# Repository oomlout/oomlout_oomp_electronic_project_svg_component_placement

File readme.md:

# SVG Component Placement in Kicad
Placing components along a path in Kicad.
##notes
Placing components along a path in Kicad.  
* ibom github: [ibom github](kicad\current_version\working\bom\ibom.html)
* ibom direct: [ibom direct](https://raw.githack.com/oomlout/oomlout_oomp_electronic_project_svg_component_placement/main/kicad/current_version/working/bom/ibom.html)

## pcb  

[board (pdf)](kicad/current_version/working/working.pdf)  

## corel working

## oomp_parts_summary
| index | designator | quantity | oomp_id | 
| --- | --- | --- | --- | 
| 1 | L2,L12,L35,L165,L51,L37,L11,L80,L14,L94,L134,L69,L193,L36,L23,L22,L180,L82,L30,L107,L181,L20,L15,L102,L55,L71,L43,L148,L145,L158,L53,L98,L166,L155,L49,L18,L146,L111,L33,L40,L81,L183,L75,L171,L143,L24,L167,L64,L38,L41,L59,L117,L105,L120,L142,L164,L84,L156,L108,L176,L130,L168,L151,L45,L114,L54,L29,L133,L42,L79,L74,L135,L144,L31,L87,L17,L66,L106,L159,L70,L149,L138,L161,L44,L123,L100,L188,L83,L6,L89,L34,L137,L67,L73,L103,L95,L60,L154,L13,L184,L16,L152,L9,L1,L190,L192,L77,L86,L173,L124,L101,L136,L194,L147,L26,L62,L179,L56,L160,L128,L196,L141,L178,L104,L115,L177,L109,L185,L191,L157,L169,L112,L10,L126,L131,L72,L19,L58,L99,L5,L91,L195,L125,L85,L27,L189,L187,L7,L57,L121,L163,L32,L93,L197,L88,L3,L186,L153,L25,L61,L21,L68,L110,L162,L119,L48,L139,L170,L47,L76,L97,L175,L50,L4,L96,L140,L113,L172,L39,L65,L90,L150,L118,L174,L78,L129,L28,L132,L52,L63,L122,L182,L92,L46,L127,L8,L116 | 197 | electronic_led_0603_red | 
| 2 | CON1 | 1 | electronic_header_2_54_mm_2_pin_through_hole | 

Search Links: (L) - lcsc, (D) - digikey, (M) - mouser, (N) - newark, (SZ) - szlcsc
note: a work on progress that takes the bom file from kicad pcb and try's to add oomp details

## positions
### top
| # Ref | Val | Package | PosX | PosY | Rot | Side | 
| --- | --- | --- | --- | --- | --- | --- | 
| CON1 | hi12pth | hi12pth_electronic_header_2_54_mm_2_pin_through_hole | -30.5 | -239.5 | 0.0 | top | 
| L1 | l6r | l6r_electronic_led_0603_red | 18.6027 | -161.0 | -135.0002 | top | 
| L2 | l6r | l6r_electronic_led_0603_red | 14.7455 | -161.0 | -135.0002 | top | 
| L3 | l6r | l6r_electronic_led_0603_red | 10.8882 | -161.0 | -135.0002 | top | 
| L4 | l6r | l6r_electronic_led_0603_red | 7.031 | -161.0 | -135.0002 | top | 
| L5 | l6r | l6r_electronic_led_0603_red | 3.1737 | -161.0 | -135.0002 | top | 
| L6 | l6r | l6r_electronic_led_0603_red | -0.6836 | -161.0 | -135.0002 | top | 
| L7 | l6r | l6r_electronic_led_0603_red | -4.5408 | -161.0 | -135.0002 | top | 
| L8 | l6r | l6r_electronic_led_0603_red | -8.3981 | -161.0 | -135.0002 | top | 
| L9 | l6r | l6r_electronic_led_0603_red | -12.2553 | -161.0 | -135.0002 | top | 
| L10 | l6r | l6r_electronic_led_0603_red | -16.1126 | -161.0 | -135.0002 | top | 
| L11 | l6r | l6r_electronic_led_0603_red | -19.9698 | -161.0 | -135.0002 | top | 
| L12 | l6r | l6r_electronic_led_0603_red | -22.45 | -162.3771 | -45.0001 | top | 
| L13 | l6r | l6r_electronic_led_0603_red | -20.8956 | -164.68 | 45.0 | top | 
| L14 | l6r | l6r_electronic_led_0603_red | -17.0384 | -164.68 | 45.0 | top | 
| L15 | l6r | l6r_electronic_led_0603_red | -13.1811 | -164.68 | 45.0 | top | 
| L16 | l6r | l6r_electronic_led_0603_red | -9.3239 | -164.68 | 45.0 | top | 
| L17 | l6r | l6r_electronic_led_0603_red | -5.4666 | -164.68 | 45.0 | top | 
| L18 | l6r | l6r_electronic_led_0603_red | -1.6093 | -164.68 | 45.0 | top | 
| L19 | l6r | l6r_electronic_led_0603_red | 2.2479 | -164.68 | 45.0 | top | 
| L20 | l6r | l6r_electronic_led_0603_red | 6.1052 | -164.68 | 45.0 | top | 
| L21 | l6r | l6r_electronic_led_0603_red | 9.9624 | -164.68 | 45.0 | top | 
| L22 | l6r | l6r_electronic_led_0603_red | 13.8324 | -164.696 | 36.9786 | top | 
| L23 | l6r | l6r_electronic_led_0603_red | 16.4655 | -167.1062 | -34.3104 | top | 
| L24 | l6r | l6r_electronic_led_0603_red | 15.5131 | -170.8008 | -66.5478 | top | 
| L25 | l6r | l6r_electronic_led_0603_red | 14.0972 | -174.3888 | -66.5202 | top | 
| L26 | l6r | l6r_electronic_led_0603_red | 12.6822 | -177.9772 | -66.5202 | top | 
| L27 | l6r | l6r_electronic_led_0603_red | 11.2673 | -181.5655 | -66.5202 | top | 
| L28 | l6r | l6r_electronic_led_0603_red | 9.8523 | -185.1539 | -66.5202 | top | 
| L29 | l6r | l6r_electronic_led_0603_red | 8.4374 | -188.7423 | -66.5202 | top | 
| L30 | l6r | l6r_electronic_led_0603_red | 7.0224 | -192.3306 | -66.5202 | top | 
| L31 | l6r | l6r_electronic_led_0603_red | 5.6075 | -195.919 | -66.5202 | top | 
| L32 | l6r | l6r_electronic_led_0603_red | 4.1925 | -199.5074 | -66.5202 | top | 
| L33 | l6r | l6r_electronic_led_0603_red | 2.7776 | -203.0957 | -66.5202 | top | 
| L34 | l6r | l6r_electronic_led_0603_red | 1.3626 | -206.6841 | -66.5202 | top | 
| L35 | l6r | l6r_electronic_led_0603_red | -0.0523 | -210.2725 | -66.5202 | top | 
| L36 | l6r | l6r_electronic_led_0603_red | -1.4673 | -213.8608 | -66.5202 | top | 
| L37 | l6r | l6r_electronic_led_0603_red | -2.8822 | -217.4492 | -66.5202 | top | 
| L38 | l6r | l6r_electronic_led_0603_red | -4.2971 | -221.0376 | -66.5202 | top | 
| L39 | l6r | l6r_electronic_led_0603_red | -5.7121 | -224.6259 | -66.5202 | top | 
| L40 | l6r | l6r_electronic_led_0603_red | -7.127 | -228.2143 | -66.5202 | top | 
| L41 | l6r | l6r_electronic_led_0603_red | -8.542 | -231.8027 | -66.5202 | top | 
| L42 | l6r | l6r_electronic_led_0603_red | -9.9569 | -235.391 | -66.5202 | top | 
| L43 | l6r | l6r_electronic_led_0603_red | -11.3719 | -238.9794 | -12.6917 | top | 
| L44 | l6r | l6r_electronic_led_0603_red | -7.5449 | -239.0 | 45.0 | top | 
| L45 | l6r | l6r_electronic_led_0603_red | -5.2221 | -236.7462 | 113.4976 | top | 
| L46 | l6r | l6r_electronic_led_0603_red | -3.8083 | -233.1574 | 113.4976 | top | 
| L47 | l6r | l6r_electronic_led_0603_red | -2.3944 | -229.5686 | 113.4976 | top | 
| L48 | l6r | l6r_electronic_led_0603_red | -0.9806 | -225.9798 | 113.4976 | top | 
| L49 | l6r | l6r_electronic_led_0603_red | 0.4333 | -222.391 | 113.4976 | top | 
| L50 | l6r | l6r_electronic_led_0603_red | 1.8471 | -218.8022 | 113.4976 | top | 
| L51 | l6r | l6r_electronic_led_0603_red | 3.261 | -215.2134 | 113.4976 | top | 
| L52 | l6r | l6r_electronic_led_0603_red | 4.6748 | -211.6246 | 113.4976 | top | 
| L53 | l6r | l6r_electronic_led_0603_red | 6.0887 | -208.0358 | 113.4976 | top | 
| L54 | l6r | l6r_electronic_led_0603_red | 7.5025 | -204.447 | 113.4976 | top | 
| L55 | l6r | l6r_electronic_led_0603_red | 8.9164 | -200.8582 | 113.4976 | top | 
| L56 | l6r | l6r_electronic_led_0603_red | 10.3302 | -197.2694 | 113.4976 | top | 
| L57 | l6r | l6r_electronic_led_0603_red | 11.744 | -193.6806 | 113.4976 | top | 
| L58 | l6r | l6r_electronic_led_0603_red | 13.1579 | -190.0918 | 113.4976 | top | 
| L59 | l6r | l6r_electronic_led_0603_red | 14.5717 | -186.503 | 113.4976 | top | 
| L60 | l6r | l6r_electronic_led_0603_red | 15.9856 | -182.9142 | 113.4976 | top | 
| L61 | l6r | l6r_electronic_led_0603_red | 17.3994 | -179.3254 | 113.4976 | top | 
| L62 | l6r | l6r_electronic_led_0603_red | 18.8133 | -175.7366 | 113.4976 | top | 
| L63 | l6r | l6r_electronic_led_0603_red | 20.2271 | -172.1478 | 113.4976 | top | 
| L64 | l6r | l6r_electronic_led_0603_red | 21.641 | -168.559 | 113.4976 | top | 
| L65 | l6r | l6r_electronic_led_0603_red | 22.46 | -164.8573 | 135.0001 | top | 
| L66 | l6r | l6r_electronic_led_0603_red | -28.46 | -155.0 | 45.0 | top | 
| L67 | l6r | l6r_electronic_led_0603_red | -23.854 | -155.0 | 45.0 | top | 
| L68 | l6r | l6r_electronic_led_0603_red | -19.2479 | -155.0 | 45.0 | top | 
| L69 | l6r | l6r_electronic_led_0603_red | -14.6419 | -155.0 | 45.0 | top | 
| L70 | l6r | l6r_electronic_led_0603_red | -10.0358 | -155.0 | 45.0 | top | 
| L71 | l6r | l6r_electronic_led_0603_red | -5.4298 | -155.0 | 45.0 | top | 
| L72 | l6r | l6r_electronic_led_0603_red | -0.8237 | -155.0 | 45.0 | top | 
| L73 | l6r | l6r_electronic_led_0603_red | 3.7823 | -155.0 | 45.0 | top | 
| L74 | l6r | l6r_electronic_led_0603_red | 8.3884 | -155.0 | 45.0 | top | 
| L75 | l6r | l6r_electronic_led_0603_red | 12.9944 | -155.0 | 45.0 | top | 
| L76 | l6r | l6r_electronic_led_0603_red | 17.6005 | -155.0 | 45.0 | top | 
| L77 | l6r | l6r_electronic_led_0603_red | 22.2065 | -155.0 | 45.0 | top | 
| L78 | l6r | l6r_electronic_led_0603_red | 26.8126 | -155.0 | 45.0 | top | 
| L79 | l6r | l6r_electronic_led_0603_red | 28.46 | -157.9586 | -45.0001 | top | 
| L80 | l6r | l6r_electronic_led_0603_red | 28.46 | -162.5646 | -45.0001 | top | 
| L81 | l6r | l6r_electronic_led_0603_red | 28.46 | -167.1707 | -51.7968 | top | 
| L82 | l6r | l6r_electronic_led_0603_red | 26.9252 | -171.4853 | -66.5048 | top | 
| L83 | l6r | l6r_electronic_led_0603_red | 25.2368 | -175.7707 | -66.5048 | top | 
| L84 | l6r | l6r_electronic_led_0603_red | 23.5483 | -180.0561 | -66.5048 | top | 
| L85 | l6r | l6r_electronic_led_0603_red | 21.8598 | -184.3415 | -66.5048 | top | 
| L86 | l6r | l6r_electronic_led_0603_red | 20.1713 | -188.6269 | -66.5048 | top | 
| L87 | l6r | l6r_electronic_led_0603_red | 18.4829 | -192.9123 | -66.5048 | top | 
| L88 | l6r | l6r_electronic_led_0603_red | 16.7944 | -197.1977 | -66.5048 | top | 
| L89 | l6r | l6r_electronic_led_0603_red | 15.1059 | -201.4831 | -66.5048 | top | 
| L90 | l6r | l6r_electronic_led_0603_red | 13.4174 | -205.7685 | -66.5048 | top | 
| L91 | l6r | l6r_electronic_led_0603_red | 11.729 | -210.0539 | -66.5048 | top | 
| L92 | l6r | l6r_electronic_led_0603_red | 10.0405 | -214.3394 | -66.5048 | top | 
| L93 | l6r | l6r_electronic_led_0603_red | 8.352 | -218.6248 | -66.5048 | top | 
| L94 | l6r | l6r_electronic_led_0603_red | 6.6635 | -222.9102 | -66.5048 | top | 
| L95 | l6r | l6r_electronic_led_0603_red | 4.9751 | -227.1956 | -66.5048 | top | 
| L96 | l6r | l6r_electronic_led_0603_red | 3.2866 | -231.481 | -66.5048 | top | 
| L97 | l6r | l6r_electronic_led_0603_red | 1.5981 | -235.7664 | -66.5048 | top | 
| L98 | l6r | l6r_electronic_led_0603_red | -0.0904 | -240.0518 | -66.5048 | top | 
| L99 | l6r | l6r_electronic_led_0603_red | -1.7789 | -244.3372 | -77.912 | top | 
| L100 | l6r | l6r_electronic_led_0603_red | -5.9337 | -245.0 | -135.0002 | top | 
| L101 | l6r | l6r_electronic_led_0603_red | -10.5397 | -245.0 | -135.0002 | top | 
| L102 | l6r | l6r_electronic_led_0603_red | -15.1457 | -245.0 | -135.0002 | top | 
| L103 | l6r | l6r_electronic_led_0603_red | -19.7518 | -245.0 | -161.549 | top | 
| L104 | l6r | l6r_electronic_led_0603_red | -18.6614 | -241.1226 | 113.4837 | top | 
| L105 | l6r | l6r_electronic_led_0603_red | -16.972 | -236.8375 | 113.4837 | top | 
| L106 | l6r | l6r_electronic_led_0603_red | -15.2827 | -232.5525 | 113.4837 | top | 
| L107 | l6r | l6r_electronic_led_0603_red | -13.5933 | -228.2674 | 113.4837 | top | 
| L108 | l6r | l6r_electronic_led_0603_red | -11.904 | -223.9824 | 113.4837 | top | 
| L109 | l6r | l6r_electronic_led_0603_red | -10.2146 | -219.6973 | 113.4837 | top | 
| L110 | l6r | l6r_electronic_led_0603_red | -8.5253 | -215.4122 | 113.4837 | top | 
| L111 | l6r | l6r_electronic_led_0603_red | -6.8359 | -211.1272 | 113.4837 | top | 
| L112 | l6r | l6r_electronic_led_0603_red | -5.1466 | -206.8421 | 113.4837 | top | 
| L113 | l6r | l6r_electronic_led_0603_red | -3.4572 | -202.557 | 113.4837 | top | 
| L114 | l6r | l6r_electronic_led_0603_red | -1.7679 | -198.272 | 113.4837 | top | 
| L115 | l6r | l6r_electronic_led_0603_red | -0.0785 | -193.9869 | 113.4837 | top | 
| L116 | l6r | l6r_electronic_led_0603_red | 1.6108 | -189.7019 | 113.4837 | top | 
| L117 | l6r | l6r_electronic_led_0603_red | 3.3001 | -185.4168 | 113.4837 | top | 
| L118 | l6r | l6r_electronic_led_0603_red | 4.9895 | -181.1317 | 113.4837 | top | 
| L119 | l6r | l6r_electronic_led_0603_red | 6.6788 | -176.8467 | 113.4837 | top | 
| L120 | l6r | l6r_electronic_led_0603_red | 8.3682 | -172.5616 | 113.4837 | top | 
| L121 | l6r | l6r_electronic_led_0603_red | 6.5265 | -170.68 | -135.0002 | top | 
| L122 | l6r | l6r_electronic_led_0603_red | 1.9205 | -170.68 | -135.0002 | top | 
| L123 | l6r | l6r_electronic_led_0603_red | -2.6856 | -170.68 | -135.0002 | top | 
| L124 | l6r | l6r_electronic_led_0603_red | -7.2916 | -170.68 | -135.0002 | top | 
| L125 | l6r | l6r_electronic_led_0603_red | -11.8977 | -170.68 | -135.0002 | top | 
| L126 | l6r | l6r_electronic_led_0603_red | -16.5037 | -170.68 | -135.0002 | top | 
| L127 | l6r | l6r_electronic_led_0603_red | -21.1098 | -170.68 | -135.0002 | top | 
| L128 | l6r | l6r_electronic_led_0603_red | -25.7158 | -170.68 | -135.0002 | top | 
| L129 | l6r | l6r_electronic_led_0603_red | -28.46 | -168.8181 | 135.0001 | top | 
| L130 | l6r | l6r_electronic_led_0603_red | -28.46 | -164.2121 | 135.0001 | top | 
| L131 | l6r | l6r_electronic_led_0603_red | -28.46 | -159.606 | 135.0001 | top | 
| L132 | l6r | l6r_electronic_led_0603_red | 25.46 | -158.0 | -135.0002 | top | 
| L133 | l6r | l6r_electronic_led_0603_red | 21.2057 | -158.0 | -135.0002 | top | 
| L134 | l6r | l6r_electronic_led_0603_red | 16.9514 | -158.0 | -135.0002 | top | 
| L135 | l6r | l6r_electronic_led_0603_red | 12.6971 | -158.0 | -135.0002 | top | 
| L136 | l6r | l6r_electronic_led_0603_red | 8.4428 | -158.0 | -135.0002 | top | 
| L137 | l6r | l6r_electronic_led_0603_red | 4.1885 | -158.0 | -135.0002 | top | 
| L138 | l6r | l6r_electronic_led_0603_red | -0.0658 | -158.0 | -135.0002 | top | 
| L139 | l6r | l6r_electronic_led_0603_red | -4.3201 | -158.0 | -135.0002 | top | 
| L140 | l6r | l6r_electronic_led_0603_red | -8.5744 | -158.0 | -135.0002 | top | 
| L141 | l6r | l6r_electronic_led_0603_red | -12.8287 | -158.0 | -135.0002 | top | 
| L142 | l6r | l6r_electronic_led_0603_red | -17.083 | -158.0 | -135.0002 | top | 
| L143 | l6r | l6r_electronic_led_0603_red | -21.3373 | -158.0 | -135.0002 | top | 
| L144 | l6r | l6r_electronic_led_0603_red | -25.46 | -158.1316 | -82.9445 | top | 
| L145 | l6r | l6r_electronic_led_0603_red | -25.46 | -162.3859 | -45.0001 | top | 
| L146 | l6r | l6r_electronic_led_0603_red | -25.46 | -166.6402 | -44.3512 | top | 
| L147 | l6r | l6r_electronic_led_0603_red | -22.2455 | -167.68 | 45.0 | top | 
| L148 | l6r | l6r_electronic_led_0603_red | -17.9911 | -167.68 | 45.0 | top | 
| L149 | l6r | l6r_electronic_led_0603_red | -13.7368 | -167.68 | 45.0 | top | 
| L150 | l6r | l6r_electronic_led_0603_red | -9.4825 | -167.68 | 45.0 | top | 
| L151 | l6r | l6r_electronic_led_0603_red | -5.2282 | -167.68 | 45.0 | top | 
| L152 | l6r | l6r_electronic_led_0603_red | -0.9739 | -167.68 | 45.0 | top | 
| L153 | l6r | l6r_electronic_led_0603_red | 3.2804 | -167.68 | 45.0 | top | 
| L154 | l6r | l6r_electronic_led_0603_red | 7.5347 | -167.68 | 45.0 | top | 
| L155 | l6r | l6r_electronic_led_0603_red | 11.789 | -167.68 | 45.0 | top | 
| L156 | l6r | l6r_electronic_led_0603_red | 12.5908 | -170.026 | -66.608 | top | 
| L157 | l6r | l6r_electronic_led_0603_red | 11.0279 | -173.9828 | -66.5112 | top | 
| L158 | l6r | l6r_electronic_led_0603_red | 9.4679 | -177.9407 | -66.5112 | top | 
| L159 | l6r | l6r_electronic_led_0603_red | 7.9079 | -181.8987 | -66.5112 | top | 
| L160 | l6r | l6r_electronic_led_0603_red | 6.348 | -185.8567 | -66.5112 | top | 
| L161 | l6r | l6r_electronic_led_0603_red | 4.788 | -189.8147 | -66.5112 | top | 
| L162 | l6r | l6r_electronic_led_0603_red | 3.228 | -193.7727 | -66.5112 | top | 
| L163 | l6r | l6r_electronic_led_0603_red | 1.668 | -197.7306 | -66.5112 | top | 
| L164 | l6r | l6r_electronic_led_0603_red | 0.1081 | -201.6886 | -66.5112 | top | 
| L165 | l6r | l6r_electronic_led_0603_red | -1.4519 | -205.6466 | -66.5112 | top | 
| L166 | l6r | l6r_electronic_led_0603_red | -3.0119 | -209.6046 | -66.5112 | top | 
| L167 | l6r | l6r_electronic_led_0603_red | -4.5718 | -213.5625 | -66.5112 | top | 
| L168 | l6r | l6r_electronic_led_0603_red | -6.1318 | -217.5205 | -66.5112 | top | 
| L169 | l6r | l6r_electronic_led_0603_red | -7.6918 | -221.4785 | -66.5112 | top | 
| L170 | l6r | l6r_electronic_led_0603_red | -9.2518 | -225.4365 | -66.5112 | top | 
| L171 | l6r | l6r_electronic_led_0603_red | -10.8117 | -229.3944 | -66.5112 | top | 
| L172 | l6r | l6r_electronic_led_0603_red | -12.3717 | -233.3524 | -66.5112 | top | 
| L173 | l6r | l6r_electronic_led_0603_red | -13.9317 | -237.3104 | -66.5112 | top | 
| L174 | l6r | l6r_electronic_led_0603_red | -15.4916 | -241.2684 | -58.1207 | top | 
| L175 | l6r | l6r_electronic_led_0603_red | -12.3121 | -242.0 | 45.0 | top | 
| L176 | l6r | l6r_electronic_led_0603_red | -8.0578 | -242.0 | 45.0 | top | 
| L177 | l6r | l6r_electronic_led_0603_red | -3.9723 | -241.752 | 88.9313 | top | 
| L178 | l6r | l6r_electronic_led_0603_red | -2.413 | -237.7938 | 113.4984 | top | 
| L179 | l6r | l6r_electronic_led_0603_red | -0.8537 | -233.8356 | 113.4984 | top | 
| L180 | l6r | l6r_electronic_led_0603_red | 0.7056 | -229.8773 | 113.4984 | top | 
| L181 | l6r | l6r_electronic_led_0603_red | 2.265 | -225.9191 | 113.4984 | top | 
| L182 | l6r | l6r_electronic_led_0603_red | 3.8243 | -221.9609 | 113.4984 | top | 
| L183 | l6r | l6r_electronic_led_0603_red | 5.3836 | -218.0026 | 113.4984 | top | 
| L184 | l6r | l6r_electronic_led_0603_red | 6.9429 | -214.0444 | 113.4984 | top | 
| L185 | l6r | l6r_electronic_led_0603_red | 8.5022 | -210.0862 | 113.4984 | top | 
| L186 | l6r | l6r_electronic_led_0603_red | 10.0616 | -206.1279 | 113.4984 | top | 
| L187 | l6r | l6r_electronic_led_0603_red | 11.6209 | -202.1697 | 113.4984 | top | 
| L188 | l6r | l6r_electronic_led_0603_red | 13.1802 | -198.2115 | 113.4984 | top | 
| L189 | l6r | l6r_electronic_led_0603_red | 14.7395 | -194.2532 | 113.4984 | top | 
| L190 | l6r | l6r_electronic_led_0603_red | 16.2988 | -190.295 | 113.4984 | top | 
| L191 | l6r | l6r_electronic_led_0603_red | 17.8582 | -186.3368 | 113.4984 | top | 
| L192 | l6r | l6r_electronic_led_0603_red | 19.4175 | -182.3785 | 113.4984 | top | 
| L193 | l6r | l6r_electronic_led_0603_red | 20.9768 | -178.4203 | 113.4984 | top | 
| L194 | l6r | l6r_electronic_led_0603_red | 22.5361 | -174.4621 | 113.4984 | top | 
| L195 | l6r | l6r_electronic_led_0603_red | 24.0954 | -170.5038 | 113.4984 | top | 
| L196 | l6r | l6r_electronic_led_0603_red | 25.46 | -166.5086 | 129.6684 | top | 
| L197 | l6r | l6r_electronic_led_0603_red | 25.46 | -162.2543 | 135.0001 | top | 

### bottom
no data

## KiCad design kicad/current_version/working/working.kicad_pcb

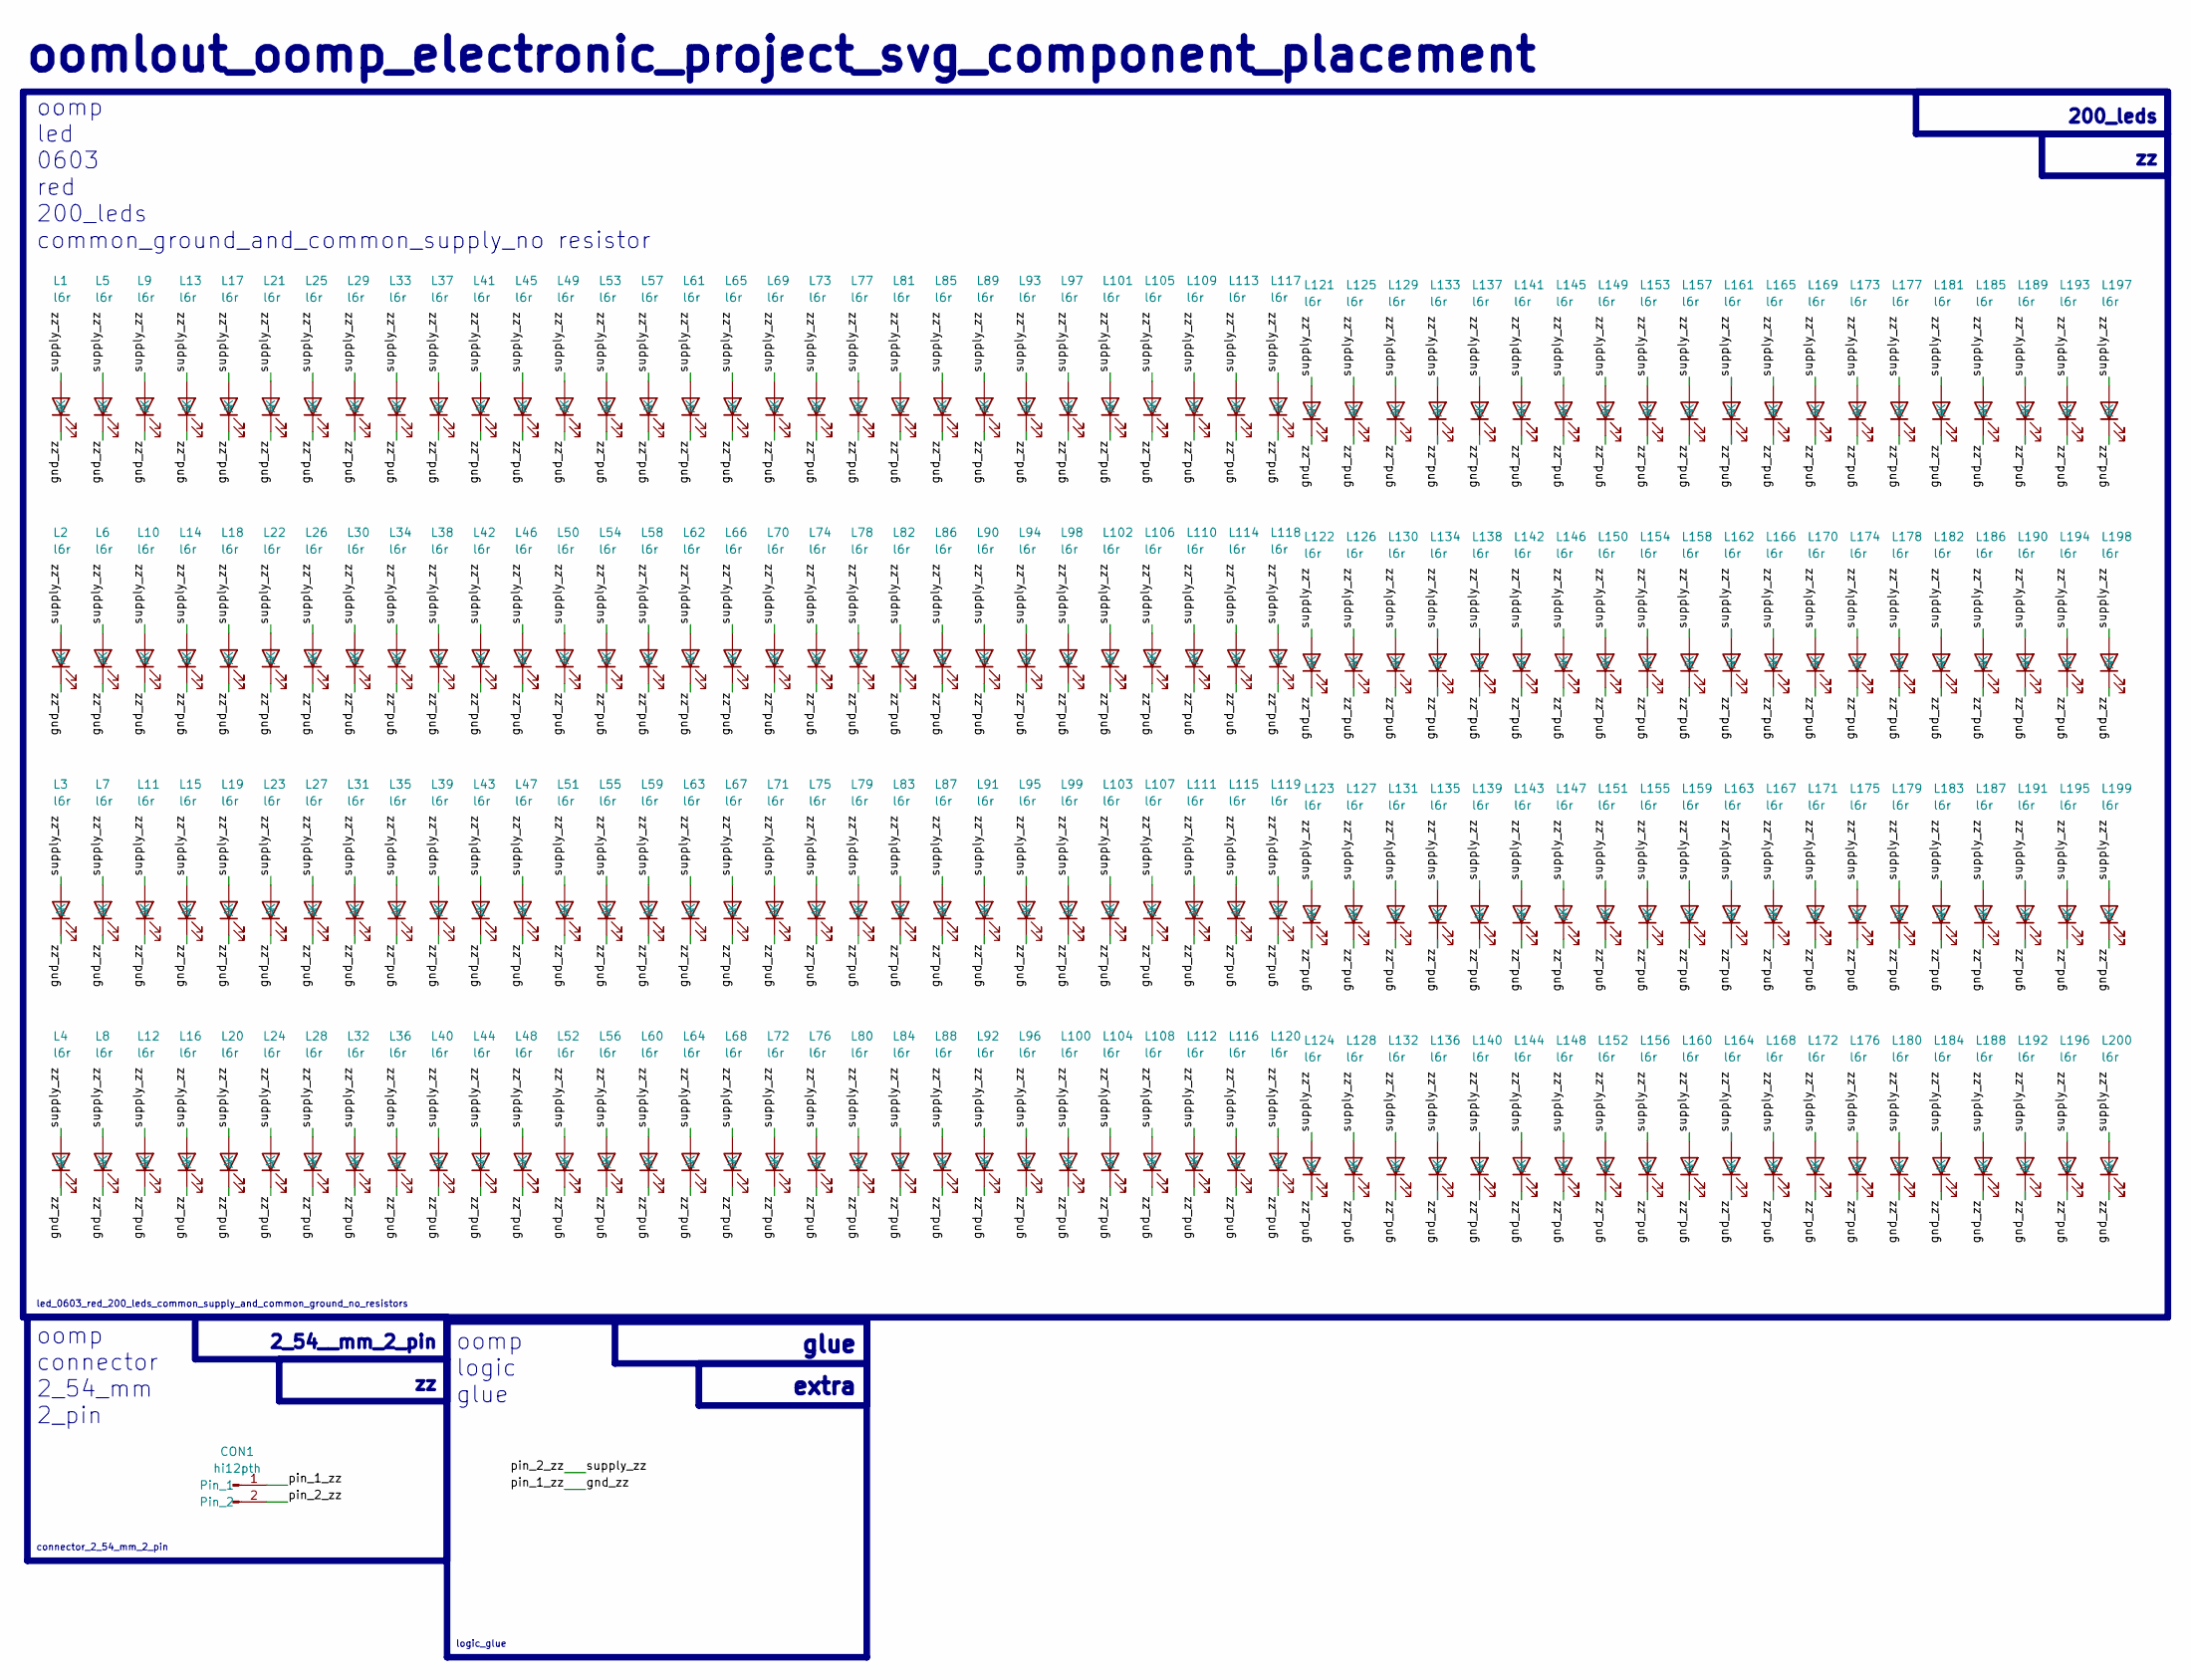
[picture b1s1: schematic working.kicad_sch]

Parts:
CON1: hi12pth; hi12pth_electronic_header_2_54_mm_2_pin_through_hole
L1, L2, L3, L4, L5, L6, L7, L8, L9, L10, L11, L12, L13, L14, L15, L16, L17, L18, L19, L20, L21, L22, L23, L24, L25, L26, L27, L28, L29, L30, L31, L32, L33, L34, L35, L36, L37, L38, L39, L40, L41, L42, L43, L44, L45, L46, L47, L48, L49, L50, L51, L52, L53, L54, L55, L56, L57, L58, L59, L60, L61, L62, L63, L64, L65, L66, L67, L68, L69, L70, L71, L72, L73, L74, L75, L76, L77, L78, L79, L80, L81, L82, L83, L84, L85, L86, L87, L88, L89, L90, L91, L92, L93, L94, L95, L96, L97, L98, L99, L100, L101, L102, L103, L104, L105, L106, L107, L108, L109, L110, L111, L112, L113, L114, L115, L116, L117, L118, L119, L120, L121, L122, L123, L124, L125, L126, L127, L128, L129, L130, L131, L132, L133, L134, L135, L136, L137, L138, L139, L140, L141, L142, L143, L144, L145, L146, L147, L148, L149, L150, L151, L152, L153, L154, L155, L156, L157, L158, L159, L160, L161, L162, L163, L164, L165, L166, L167, L168, L169, L170, L171, L172, L173, L174, L175, L176, L177, L178, L179, L180, L181, L182, L183, L184, L185, L186, L187, L188, L189, L190, L191, L192, L193, L194, L195, L196, L197, L198, L199, L200: l6r; l6r_electronic_led_0603_red

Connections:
/gnd_zz: CON1.1, L1.1 (K), L2.1 (K), L3.1 (K), L4.1 (K), L5.1 (K), L6.1 (K), L7.1 (K), L8.1 (K), L9.1 (K), L10.1 (K), L11.1 (K), L12.1 (K), L13.1 (K), L14.1 (K), L15.1 (K), L16.1 (K), L17.1 (K), L18.1 (K), L19.1 (K), L20.1 (K), L21.1 (K), L22.1 (K), L23.1 (K), L24.1 (K), L25.1 (K), L26.1 (K), L27.1 (K), L28.1 (K), L29.1 (K), L30.1 (K), L31.1 (K), L32.1 (K), L33.1 (K), L34.1 (K), L35.1 (K), L36.1 (K), L37.1 (K), L38.1 (K), L39.1 (K), L40.1 (K), L41.1 (K), L42.1 (K), L43.1 (K), L44.1 (K), L45.1 (K), L46.1 (K), L47.1 (K), L48.1 (K), L49.1 (K), L50.1 (K), L51.1 (K), L52.1 (K), L53.1 (K), L54.1 (K), L55.1 (K), L56.1 (K), L57.1 (K), L58.1 (K), L59.1 (K), L60.1 (K), L61.1 (K), L62.1 (K), L63.1 (K), L64.1 (K), L65.1 (K), L66.1 (K), L67.1 (K), L68.1 (K), L69.1 (K), L70.1 (K), L71.1 (K), L72.1 (K), L73.1 (K), L74.1 (K), L75.1 (K), L76.1 (K), L77.1 (K), L78.1 (K), L79.1 (K), L80.1 (K), L81.1 (K), L82.1 (K), L83.1 (K), L84.1 (K), L85.1 (K), L86.1 (K), L87.1 (K), L88.1 (K), L89.1 (K), L90.1 (K), L91.1 (K), L92.1 (K), L93.1 (K), L94.1 (K), L95.1 (K), L96.1 (K), L97.1 (K), L98.1 (K), L99.1 (K), L100.1 (K), L101.1 (K), L102.1 (K), L103.1 (K), L104.1 (K), L105.1 (K), L106.1 (K), L107.1 (K), L108.1 (K), L109.1 (K), L110.1 (K), L111.1 (K), L112.1 (K), L113.1 (K), L114.1 (K), L115.1 (K), L116.1 (K), L117.1 (K), L118.1 (K), L119.1 (K), L120.1 (K), L121.1 (K), L122.1 (K), L123.1 (K), L124.1 (K), L125.1 (K), L126.1 (K), L127.1 (K), L128.1 (K), L129.1 (K), L130.1 (K), L131.1 (K), L132.1 (K), L133.1 (K), L134.1 (K), L135.1 (K), L136.1 (K), L137.1 (K), L138.1 (K), L139.1 (K), L140.1 (K), L141.1 (K), L142.1 (K), L143.1 (K), L144.1 (K), L145.1 (K), L146.1 (K), L147.1 (K), L148.1 (K), L149.1 (K), L150.1 (K), L151.1 (K), L152.1 (K), L153.1 (K), L154.1 (K), L155.1 (K), L156.1 (K), L157.1 (K), L158.1 (K), L159.1 (K), L160.1 (K), L161.1 (K), L162.1 (K), L163.1 (K), L164.1 (K), L165.1 (K), L166.1 (K), L167.1 (K), L168.1 (K), L169.1 (K), L170.1 (K), L171.1 (K), L172.1 (K), L173.1 (K), L174.1 (K), L175.1 (K), L176.1 (K), L177.1 (K), L178.1 (K), L179.1 (K), L180.1 (K), L181.1 (K), L182.1 (K), L183.1 (K), L184.1 (K), L185.1 (K), L186.1 (K), L187.1 (K), L188.1 (K), L189.1 (K), L190.1 (K), L191.1 (K), L192.1 (K), L193.1 (K), L194.1 (K), L195.1 (K), L196.1 (K), L197.1 (K), L200.1 (K)
/pin_2_zz: CON1.2, L1.2 (A), L2.2 (A), L3.2 (A), L4.2 (A), L5.2 (A), L6.2 (A), L7.2 (A), L8.2 (A), L9.2 (A), L10.2 (A), L11.2 (A), L12.2 (A), L13.2 (A), L14.2 (A), L15.2 (A), L16.2 (A), L17.2 (A), L18.2 (A), L19.2 (A), L20.2 (A), L21.2 (A), L22.2 (A), L23.2 (A), L24.2 (A), L25.2 (A), L26.2 (A), L27.2 (A), L28.2 (A), L29.2 (A), L30.2 (A), L31.2 (A), L32.2 (A), L33.2 (A), L34.2 (A), L35.2 (A), L36.2 (A), L37.2 (A), L38.2 (A), L39.2 (A), L40.2 (A), L41.2 (A), L42.2 (A), L43.2 (A), L44.2 (A), L45.2 (A), L46.2 (A), L47.2 (A), L48.2 (A), L49.2 (A), L50.2 (A), L51.2 (A), L52.2 (A), L53.2 (A), L54.2 (A), L55.2 (A), L56.2 (A), L57.2 (A), L58.2 (A), L59.2 (A), L60.2 (A), L61.2 (A), L62.2 (A), L63.2 (A), L64.2 (A), L65.2 (A), L66.2 (A), L67.2 (A), L68.2 (A), L69.2 (A), L70.2 (A), L71.2 (A), L72.2 (A), L73.2 (A), L74.2 (A), L75.2 (A), L76.2 (A), L77.2 (A), L78.2 (A), L79.2 (A), L80.2 (A), L81.2 (A), L82.2 (A), L83.2 (A), L84.2 (A), L85.2 (A), L86.2 (A), L87.2 (A), L88.2 (A), L89.2 (A), L90.2 (A), L91.2 (A), L92.2 (A), L93.2 (A), L94.2 (A), L95.2 (A), L96.2 (A), L97.2 (A), L98.2 (A), L99.2 (A), L100.2 (A), L101.2 (A), L102.2 (A), L103.2 (A), L104.2 (A), L105.2 (A), L106.2 (A), L107.2 (A), L108.2 (A), L109.2 (A), L110.2 (A), L111.2 (A), L112.2 (A), L113.2 (A), L114.2 (A), L115.2 (A), L116.2 (A), L117.2 (A), L118.2 (A), L119.2 (A), L120.2 (A), L121.2 (A), L122.2 (A), L123.2 (A), L124.2 (A), L125.2 (A), L126.2 (A), L127.2 (A), L128.2 (A), L129.2 (A), L130.2 (A), L131.2 (A), L132.2 (A), L133.2 (A), L134.2 (A), L135.2 (A), L136.2 (A), L137.2 (A), L138.2 (A), L139.2 (A), L140.2 (A), L141.2 (A), L142.2 (A), L143.2 (A), L144.2 (A), L145.2 (A), L146.2 (A), L147.2 (A), L148.2 (A), L149.2 (A), L150.2 (A), L151.2 (A), L152.2 (A), L153.2 (A), L154.2 (A), L155.2 (A), L156.2 (A), L157.2 (A), L158.2 (A), L159.2 (A), L160.2 (A), L161.2 (A), L162.2 (A), L163.2 (A), L164.2 (A), L165.2 (A), L166.2 (A), L167.2 (A), L168.2 (A), L169.2 (A), L170.2 (A), L171.2 (A), L172.2 (A), L173.2 (A), L174.2 (A), L175.2 (A), L176.2 (A), L177.2 (A), L178.2 (A), L179.2 (A), L180.2 (A), L181.2 (A), L182.2 (A), L183.2 (A), L184.2 (A), L185.2 (A), L186.2 (A), L187.2 (A), L188.2 (A), L189.2 (A), L190.2 (A), L191.2 (A), L192.2 (A), L193.2 (A), L194.2 (A), L195.2 (A), L196.2 (A), L197.2 (A), L200.2 (A)

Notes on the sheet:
oomp connector 2_54_mm 2_pin
glue
2_54__mm_2_pin
led_0603_red_200_leds_common_supply_and_common_ground_no_resistors
extra
200_leds
oomp led 0603 red 200_leds common_ground_and_common_supply_no resistor
logic_glue
connector_2_54_mm_2_pin
oomlout_oomp_electronic_project_svg_component_placement
oomp logic glue

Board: 2 copper layers, 198 parts (0 on the bottom side), 2 nets, no tracks yet.

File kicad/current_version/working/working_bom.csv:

"Id";"Designator";"Footprint";"Quantity";"Designation";"Supplier and ref";
1;"L2,L12,L35,L165,L51,L37,L11,L80,L14,L94,L134,L69,L193,L36,L23,L22,L180,L82,L30,L107,L181,L20,L15,L102,L55,L71,L43,L148,L145,L158,L53,L98,L166,L155,L49,L18,L146,L111,L33,L40,L81,L183,L75,L171,L143,L24,L167,L64,L38,L41,L59,L117,L105,L120,L142,L164,L84,L156,L108,L176,L130,L168,L151,L45,L114,L54,L29,L133,L42,L79,L74,L135,L144,L31,L87,L17,L66,L106,L159,L70,L149,L138,L161,L44,L123,L100,L188,L83,L6,L89,L34,L137,L67,L73,L103,L95,L60,L154,L13,L184,L16,L152,L9,L1,L190,L192,L77,L86,L173,L124,L101,L136,L194,L147,L26,L62,L179,L56,L160,L128,L196,L141,L178,L104,L115,L177,L109,L185,L191,L157,L169,L112,L10,L126,L131,L72,L19,L58,L99,L5,L91,L195,L125,L85,L27,L189,L187,L7,L57,L121,L163,L32,L93,L197,L88,L3,L186,L153,L25,L61,L21,L68,L110,L162,L119,L48,L139,L170,L47,L76,L97,L175,L50,L4,L96,L140,L113,L172,L39,L65,L90,L150,L118,L174,L78,L129,L28,L132,L52,L63,L122,L182,L92,L46,L127,L8,L116";"l6r_electronic_led_0603_red";197;"l6r";;;
2;"CON1";"hi12pth_electronic_header_2_54_mm_2_pin_through_hole";1;"hi12pth";;;

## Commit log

2023-09-20 initial
2023-09-20 working to a 7
2023-09-20 commiting after auto generation
